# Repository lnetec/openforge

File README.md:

# openforge
OpenForge is Beaglebone Black clone in Kicad.

BeagleBone® Black Industrial answers the need for an industrial rated single board computer with extended temperature range of -40°C to +85°C.
This project aims to bring Beaglebone Black to Kicad ,an excellent open source EDA, world.

Current status:
1. All schematics have been ported to kicad. Component references match original Beaglebone Black.
2. Footprints assigned to all parts.
3. PCB have been created, all componets placed automatically with the help of a python script.

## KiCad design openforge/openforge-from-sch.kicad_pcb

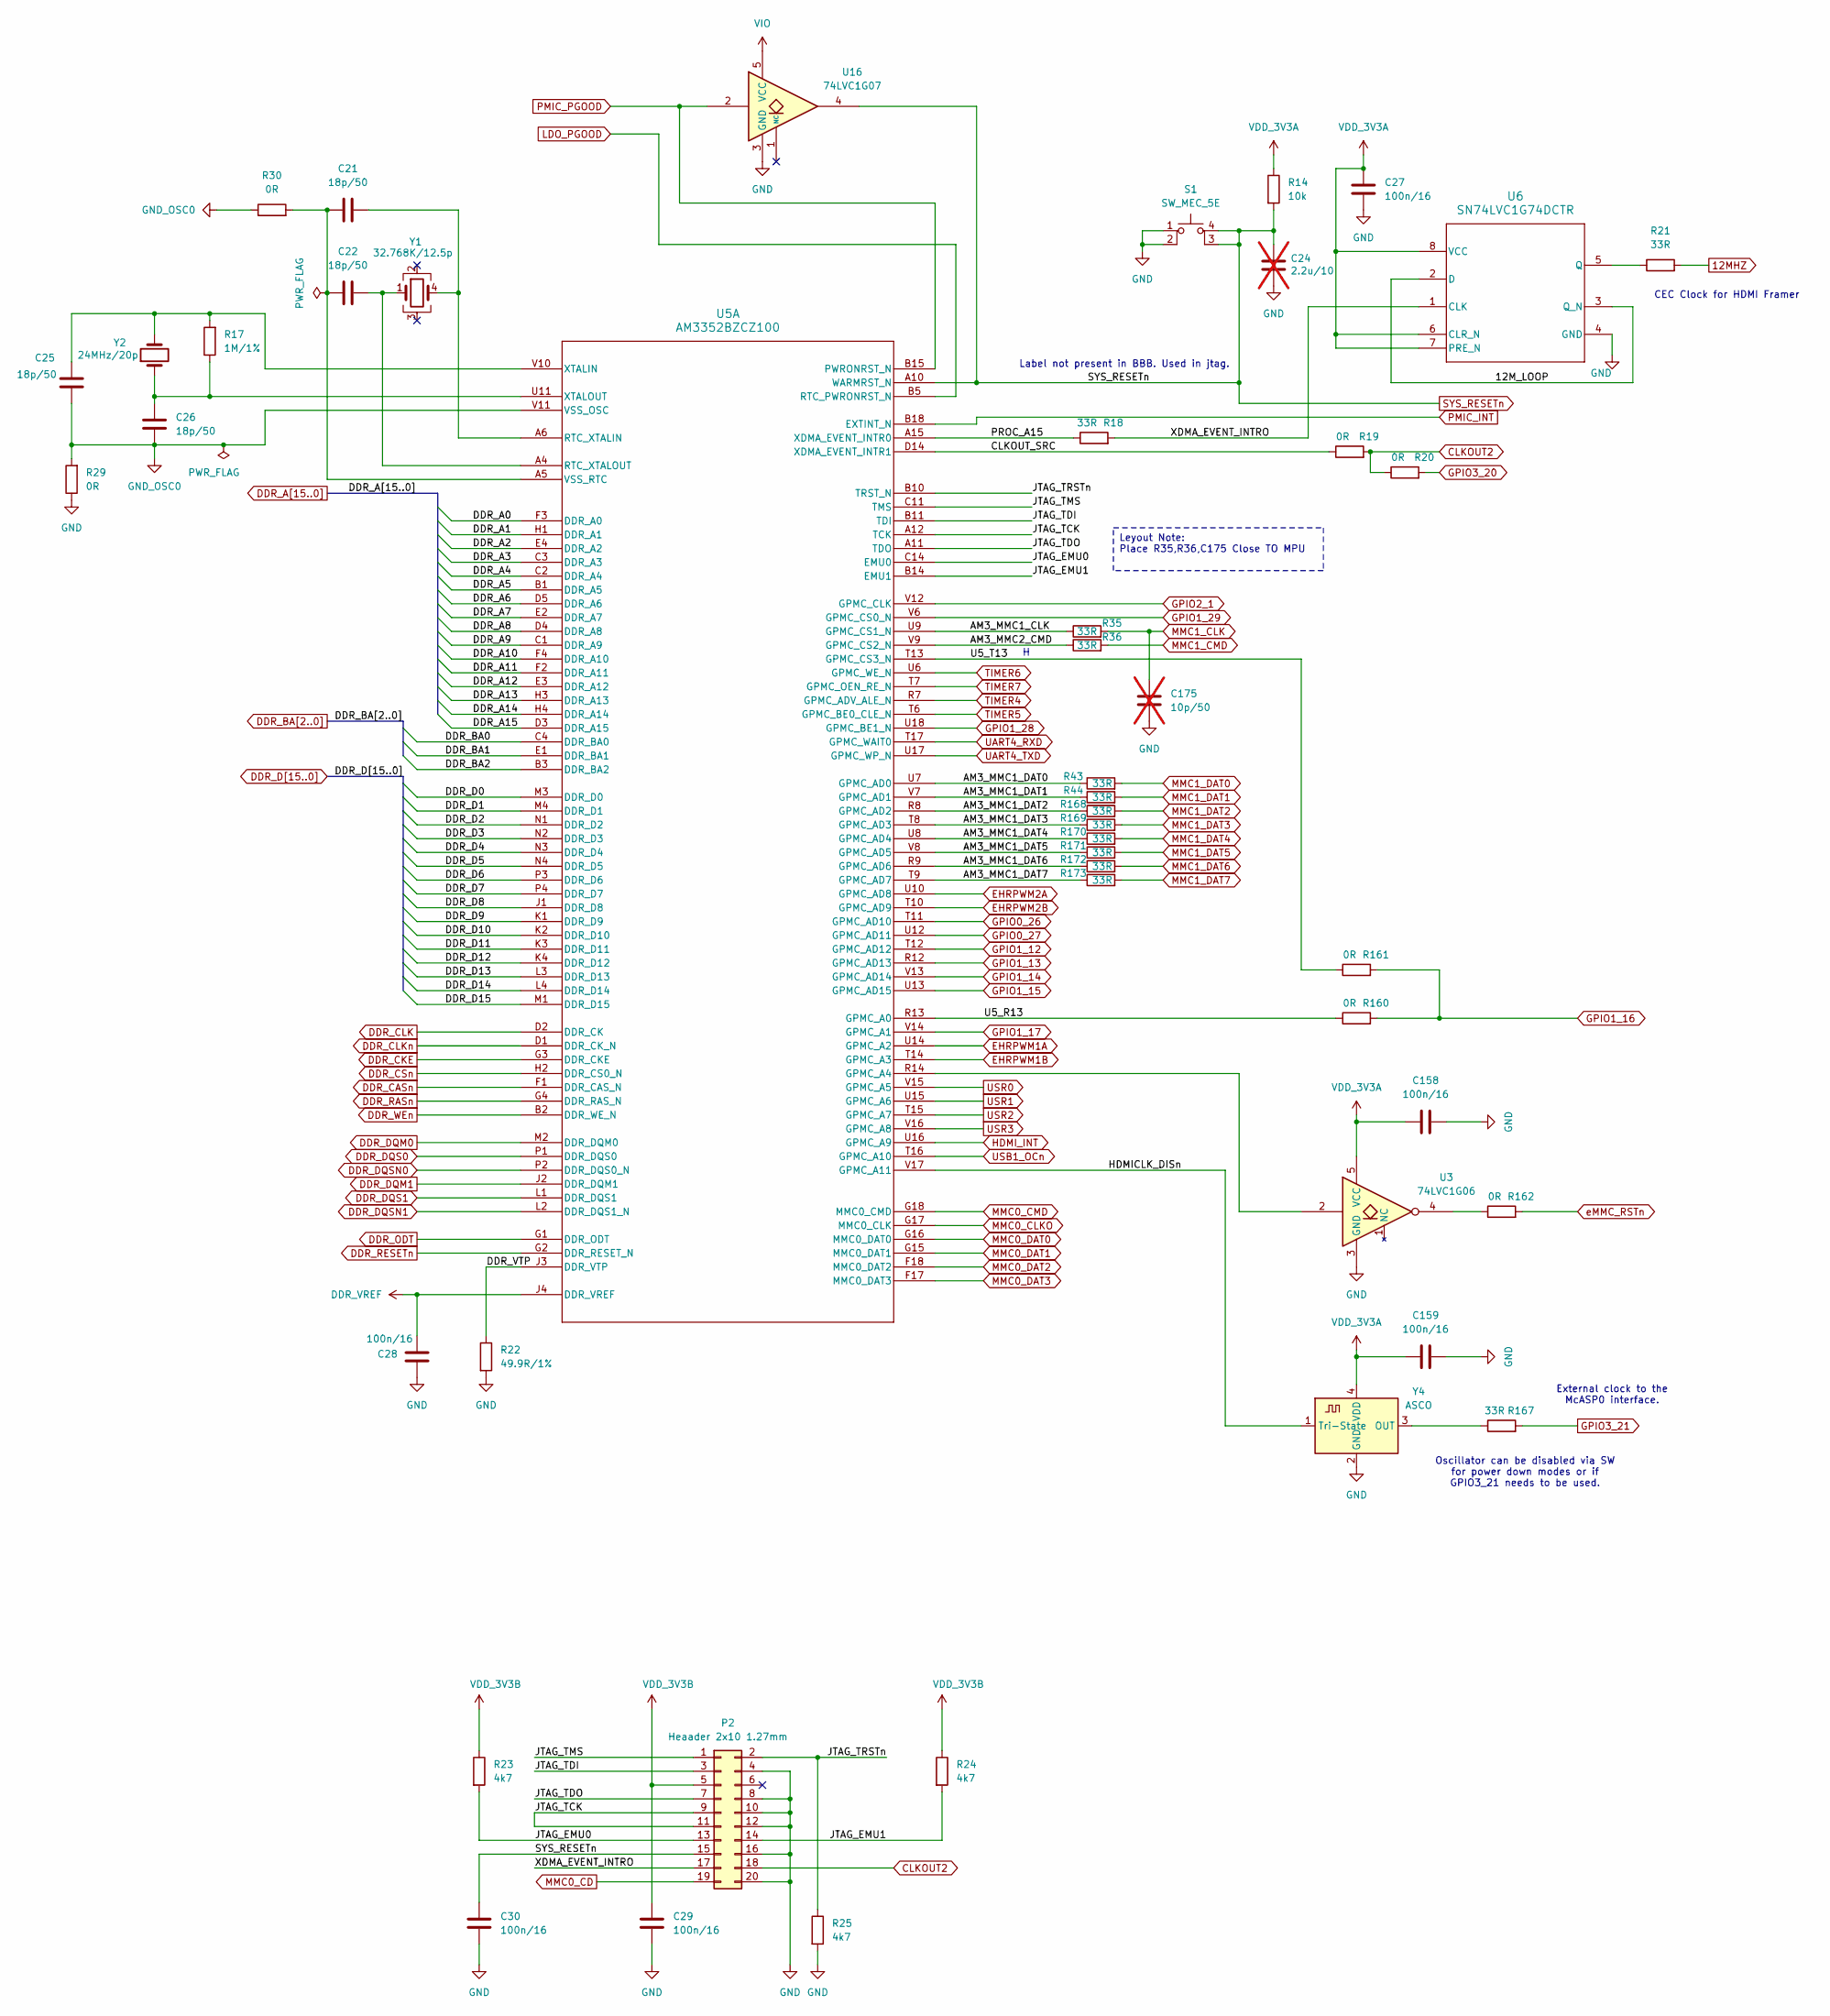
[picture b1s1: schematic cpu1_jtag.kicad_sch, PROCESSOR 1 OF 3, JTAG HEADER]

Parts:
C21, C22, C25, C26: 18p/50; C_0402_1005Metric
C24: 2.2u/10; C_0402_1005Metric; not fitted
C27, C28, C29, C30, C158, C159: 100n/16; C_0402_1005Metric
C175: 10p/50; C_0402_1005Metric; not fitted
P2: Heaader 2x10 1.27mm; PinHeader_2x10_P1.27mm_Vertical_SMD
R14: 10k; R_0402_1005Metric
R17: 1M/1%; R_0402_1005Metric
R18, R21, R35, R36, R43, R44, R167, R168, R169, R170, R171, R172, R173: 33R; R_0402_1005Metric
R19, R20, R29, R30, R160, R161, R162: 0R; R_0402_1005Metric
R22: 49.9R/1%; R_0402_1005Metric
R23, R24, R25: 4k7; R_0402_1005Metric
S1: SW_MEC_5E; KMR2xxG_CNK
U3: 74LVC1G06; DCK0005A_L
U5: AM3352BZCZ100; ZCZ0324A
U6: SN74LVC1G74DCTR; DCT0008A_L
U16: 74LVC1G07; DCK0005A_L
Y1: 32.768K/12.5p; Crystal_SMD_5032-4Pin_5.0x3.2mm
Y2: 24MHz/20p; Crystal_SMD_Abracon_ABM7-2Pin_6.0x3.5mm
Y4: ASCO; Oscillator_SMD_Abracon_ASCO-4Pin_1.6x1.2mm

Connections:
12MHZ: R21.2; also elsewhere on the board
/CPU1 And JTAG/12M_LOOP: U6.2 (D), U6.3 (Q_N)
/CPU1 And JTAG/AM3_MMC1_CLK: R35.1, U5.U9 (GPMC_CS1_N)
/CPU1 And JTAG/AM3_MMC1_DAT0: R43.1, U5.U7 (GPMC_AD0)
/CPU1 And JTAG/AM3_MMC1_DAT1: R44.1, U5.V7 (GPMC_AD1)
/CPU1 And JTAG/AM3_MMC1_DAT2: R168.1, U5.R8 (GPMC_AD2)
/CPU1 And JTAG/AM3_MMC1_DAT3: R169.1, U5.T8 (GPMC_AD3)
/CPU1 And JTAG/AM3_MMC1_DAT4: R170.1, U5.U8 (GPMC_AD4)
/CPU1 And JTAG/AM3_MMC1_DAT5: R171.1, U5.V8 (GPMC_AD5)
/CPU1 And JTAG/AM3_MMC1_DAT6: R172.1, U5.R9 (GPMC_AD6)
/CPU1 And JTAG/AM3_MMC1_DAT7: R173.1, U5.T9 (GPMC_AD7)
/CPU1 And JTAG/AM3_MMC2_CMD: R36.1, U5.V9 (GPMC_CS2_N)
/CPU1 And JTAG/CLKOUT_SRC: R19.1, U5.D14 (XDMA_EVENT_INTR1)
/CPU1 And JTAG/DDR_VTP: R22.1, U5.J3 (DDR_VTP)
/CPU1 And JTAG/HDMICLK_DISn: U5.V17 (GPMC_A11), Y4.1 (Tri-State)
/CPU1 And JTAG/JTAG_EMU0: P2.13, R23.2, U5.C14 (EMU0)
/CPU1 And JTAG/JTAG_EMU1: P2.14, R24.2, U5.B14 (EMU1)
/CPU1 And JTAG/JTAG_TCK: P2.9, P2.11, U5.A12 (TCK)
/CPU1 And JTAG/JTAG_TDI: P2.3, U5.B11 (TDI)
/CPU1 And JTAG/JTAG_TDO: P2.7, U5.A11 (TDO)
/CPU1 And JTAG/JTAG_TMS: P2.1, U5.C11 (TMS)
/CPU1 And JTAG/JTAG_TRSTn: P2.2, R25.1, U5.B10 (TRST_N)
/CPU1 And JTAG/PROC_A15: R18.1, U5.A15 (XDMA_EVENT_INTR0)
/CPU1 And JTAG/U5_R13: R160.1, U5.R13 (GPMC_A0)
/CPU1 And JTAG/U5_T13: R161.1, U5.T13 (GPMC_CS3_N)
/CPU1 And JTAG/XDMA_EVENT_INTRO: P2.17, R18.2, U6.1 (CLK)
CLKOUT2: P2.18, R19.2, R20.1; also elsewhere on the board
DDR_A0: U5.F3 (DDR_A0); also elsewhere on the board
DDR_A1: U5.H1 (DDR_A1); also elsewhere on the board
DDR_A2: U5.E4 (DDR_A2); also elsewhere on the board
DDR_A3: U5.C3 (DDR_A3); also elsewhere on the board
DDR_A4: U5.C2 (DDR_A4); also elsewhere on the board
DDR_A5: U5.B1 (DDR_A5); also elsewhere on the board
DDR_A6: U5.D5 (DDR_A6); also elsewhere on the board
DDR_A7: U5.E2 (DDR_A7); also elsewhere on the board
DDR_A8: U5.D4 (DDR_A8); also elsewhere on the board
DDR_A9: U5.C1 (DDR_A9); also elsewhere on the board
DDR_A10: U5.F4 (DDR_A10); also elsewhere on the board
DDR_A11: U5.F2 (DDR_A11); also elsewhere on the board
DDR_A12: U5.E3 (DDR_A12); also elsewhere on the board
DDR_A13: U5.H3 (DDR_A13); also elsewhere on the board
DDR_A14: U5.H4 (DDR_A14); also elsewhere on the board
DDR_A15: U5.D3 (DDR_A15); also elsewhere on the board
DDR_BA0: U5.C4 (DDR_BA0); also elsewhere on the board
DDR_BA1: U5.E1 (DDR_BA1); also elsewhere on the board
DDR_BA2: U5.B3 (DDR_BA2); also elsewhere on the board
DDR_CASn: U5.F1 (DDR_CAS_N); also elsewhere on the board
DDR_CKE: U5.G3 (DDR_CKE); also elsewhere on the board
DDR_CLK: U5.D2 (DDR_CK); also elsewhere on the board
DDR_CLKn: U5.D1 (DDR_CK_N); also elsewhere on the board
DDR_CSn: U5.H2 (DDR_CS0_N); also elsewhere on the board
DDR_D0: U5.M3 (DDR_D0); also elsewhere on the board
DDR_D1: U5.M4 (DDR_D1); also elsewhere on the board
DDR_D2: U5.N1 (DDR_D2); also elsewhere on the board
DDR_D3: U5.N2 (DDR_D3); also elsewhere on the board
DDR_D4: U5.N3 (DDR_D4); also elsewhere on the board
DDR_D5: U5.N4 (DDR_D5); also elsewhere on the board
DDR_D6: U5.P3 (DDR_D6); also elsewhere on the board
DDR_D7: U5.P4 (DDR_D7); also elsewhere on the board
DDR_D8: U5.J1 (DDR_D8); also elsewhere on the board
DDR_D9: U5.K1 (DDR_D9); also elsewhere on the board
DDR_D10: U5.K2 (DDR_D10); also elsewhere on the board
DDR_D11: U5.K3 (DDR_D11); also elsewhere on the board
DDR_D12: U5.K4 (DDR_D12); also elsewhere on the board
DDR_D13: U5.L3 (DDR_D13); also elsewhere on the board
DDR_D14: U5.L4 (DDR_D14); also elsewhere on the board
DDR_D15: U5.M1 (DDR_D15); also elsewhere on the board
DDR_DQM0: U5.M2 (DDR_DQM0); also elsewhere on the board
DDR_DQM1: U5.J2 (DDR_DQM1); also elsewhere on the board
DDR_DQS0: U5.P1 (DDR_DQS0); also elsewhere on the board
DDR_DQS1: U5.L1 (DDR_DQS1); also elsewhere on the board
DDR_DQSN0: U5.P2 (DDR_DQS0_N); also elsewhere on the board
DDR_DQSN1: U5.L2 (DDR_DQS1_N); also elsewhere on the board
DDR_ODT: U5.G1 (DDR_ODT); also elsewhere on the board
DDR_RASn: U5.G4 (DDR_RAS_N); also elsewhere on the board
DDR_RESETn: U5.G2 (DDR_RESET_N); also elsewhere on the board
DDR_VREF: C28.1, U5.J4 (DDR_VREF); also elsewhere on the board
DDR_WEn: U5.B2 (DDR_WE_N); also elsewhere on the board
EHRPWM1A: U5.U14 (GPMC_A2); also elsewhere on the board
EHRPWM1B: U5.T14 (GPMC_A3); also elsewhere on the board
EHRPWM2A: U5.U10 (GPMC_AD8); also elsewhere on the board
EHRPWM2B: U5.T10 (GPMC_AD9); also elsewhere on the board
GND: C24.2, C27.2, C28.2, C29.1, C30.1, C158.2, C159.2, C175.2, P2.4, P2.8, P2.10, P2.12, P2.16, P2.20, R22.2, R25.2, R29.1, S1.1, S1.2, U3.3 (GND), U6.4 (GND), U16.3 (GND), Y4.2 (GND); also elsewhere on the board
GND_OSC0: C25.1, C26.1, R29.2, R30.1, U5.V11 (VSS_OSC)
GPIO0_26: U5.T11 (GPMC_AD10); also elsewhere on the board
GPIO0_27: U5.U12 (GPMC_AD11); also elsewhere on the board
GPIO1_12: U5.T12 (GPMC_AD12); also elsewhere on the board
GPIO1_13: U5.R12 (GPMC_AD13); also elsewhere on the board
GPIO1_14: U5.V13 (GPMC_AD14); also elsewhere on the board
GPIO1_15: U5.U13 (GPMC_AD15); also elsewhere on the board
GPIO1_16: R160.2, R161.2; also elsewhere on the board
GPIO1_17: U5.V14 (GPMC_A1); also elsewhere on the board
GPIO1_28: U5.U18 (GPMC_BE1_N); also elsewhere on the board
GPIO1_29: U5.V6 (GPMC_CS0_N); also elsewhere on the board
GPIO2_1: U5.V12 (GPMC_CLK); also elsewhere on the board
GPIO3_20: R20.2; also elsewhere on the board
GPIO3_21: R167.2; also elsewhere on the board
HDMI_INT: U5.U16 (GPMC_A9); also elsewhere on the board
LDO_PGOOD: U5.B5 (RTC_PWRONRST_N); also elsewhere on the board
MMC0_CD: P2.19; also elsewhere on the board
MMC0_CLKO: U5.G17 (MMC0_CLK); also elsewhere on the board
MMC0_CMD: U5.G18 (MMC0_CMD); also elsewhere on the board
MMC0_DAT0: U5.G16 (MMC0_DAT0); also elsewhere on the board
MMC0_DAT1: U5.G15 (MMC0_DAT1); also elsewhere on the board
MMC0_DAT2: U5.F18 (MMC0_DAT2); also elsewhere on the board
MMC0_DAT3: U5.F17 (MMC0_DAT3); also elsewhere on the board
MMC1_CLK: C175.1, R35.2; also elsewhere on the board
MMC1_CMD: R36.2; also elsewhere on the board
MMC1_DAT0: R43.2; also elsewhere on the board
MMC1_DAT1: R44.2; also elsewhere on the board
MMC1_DAT2: R168.2; also elsewhere on the board
MMC1_DAT3: R169.2; also elsewhere on the board
MMC1_DAT4: R170.2; also elsewhere on the board
MMC1_DAT5: R171.2; also elsewhere on the board
MMC1_DAT6: R172.2; also elsewhere on the board
MMC1_DAT7: R173.2; also elsewhere on the board
unnamed: R162.1, U3.4
unnamed: U3.2, U5.R14 (GPMC_A4)
unnamed: C21.2, U5.A6 (RTC_XTALIN), Y1.4
unnamed: C22.2, U5.A4 (RTC_XTALOUT), Y1.1
unnamed: C21.1, C22.1, R30.2, U5.A5 (VSS_RTC)
unnamed: C25.2, R17.2, U5.V10 (XTALIN), Y2.2
unnamed: C26.2, R17.1, U5.U11 (XTALOUT), Y2.1
unnamed: R21.1, U6.5 (Q)
unnamed: R167.1, Y4.3 (OUT)
PMIC_INT: U5.B18 (EXTINT_N); also elsewhere on the board
PMIC_PGOOD: U5.B15 (PWRONRST_N), U16.2; also elsewhere on the board
SYS_RESETn: C24.1, C30.2, P2.15, R14.2, S1.3 (K), S1.4 (A), U5.A10 (WARMRST_N), U16.4; also elsewhere on the board
TIMER4: U5.R7 (GPMC_ADV_ALE_N); also elsewhere on the board
TIMER5: U5.T6 (GPMC_BE0_CLE_N); also elsewhere on the board
TIMER6: U5.U6 (GPMC_WE_N); also elsewhere on the board
TIMER7: U5.T7 (GPMC_OEN_RE_N); also elsewhere on the board
UART4_RXD: U5.T17 (GPMC_WAIT0); also elsewhere on the board
UART4_TXD: U5.U17 (GPMC_WP_N); also elsewhere on the board
USB1_OCn: U5.T16 (GPMC_A10); also elsewhere on the board
USR0: U5.V15 (GPMC_A5); also elsewhere on the board
USR1: U5.U15 (GPMC_A6); also elsewhere on the board
USR2: U5.T15 (GPMC_A7); also elsewhere on the board
USR3: U5.V16 (GPMC_A8); also elsewhere on the board
VDD_3V3A: C27.1, C158.1, C159.1, R14.1, U3.5 (VCC), U6.6 (CLR_N), U6.7 (PRE_N), U6.8 (VCC), Y4.4 (VDD); also elsewhere on the board
VDD_3V3B: C29.2, P2.5, R23.1, R24.1; also elsewhere on the board
VIO: U16.5 (VCC); also elsewhere on the board
eMMC_RSTn: R162.2; also elsewhere on the board

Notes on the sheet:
Leyout Note: Place R35,R36,C175 Close TO MPU
External clock to the McASP0 interface.
CEC Clock for HDMI Framer
Label not present in BBB. Used in jtag.
Oscillator can be disabled via SW for power down modes or if GPIO3_21 needs to be used.

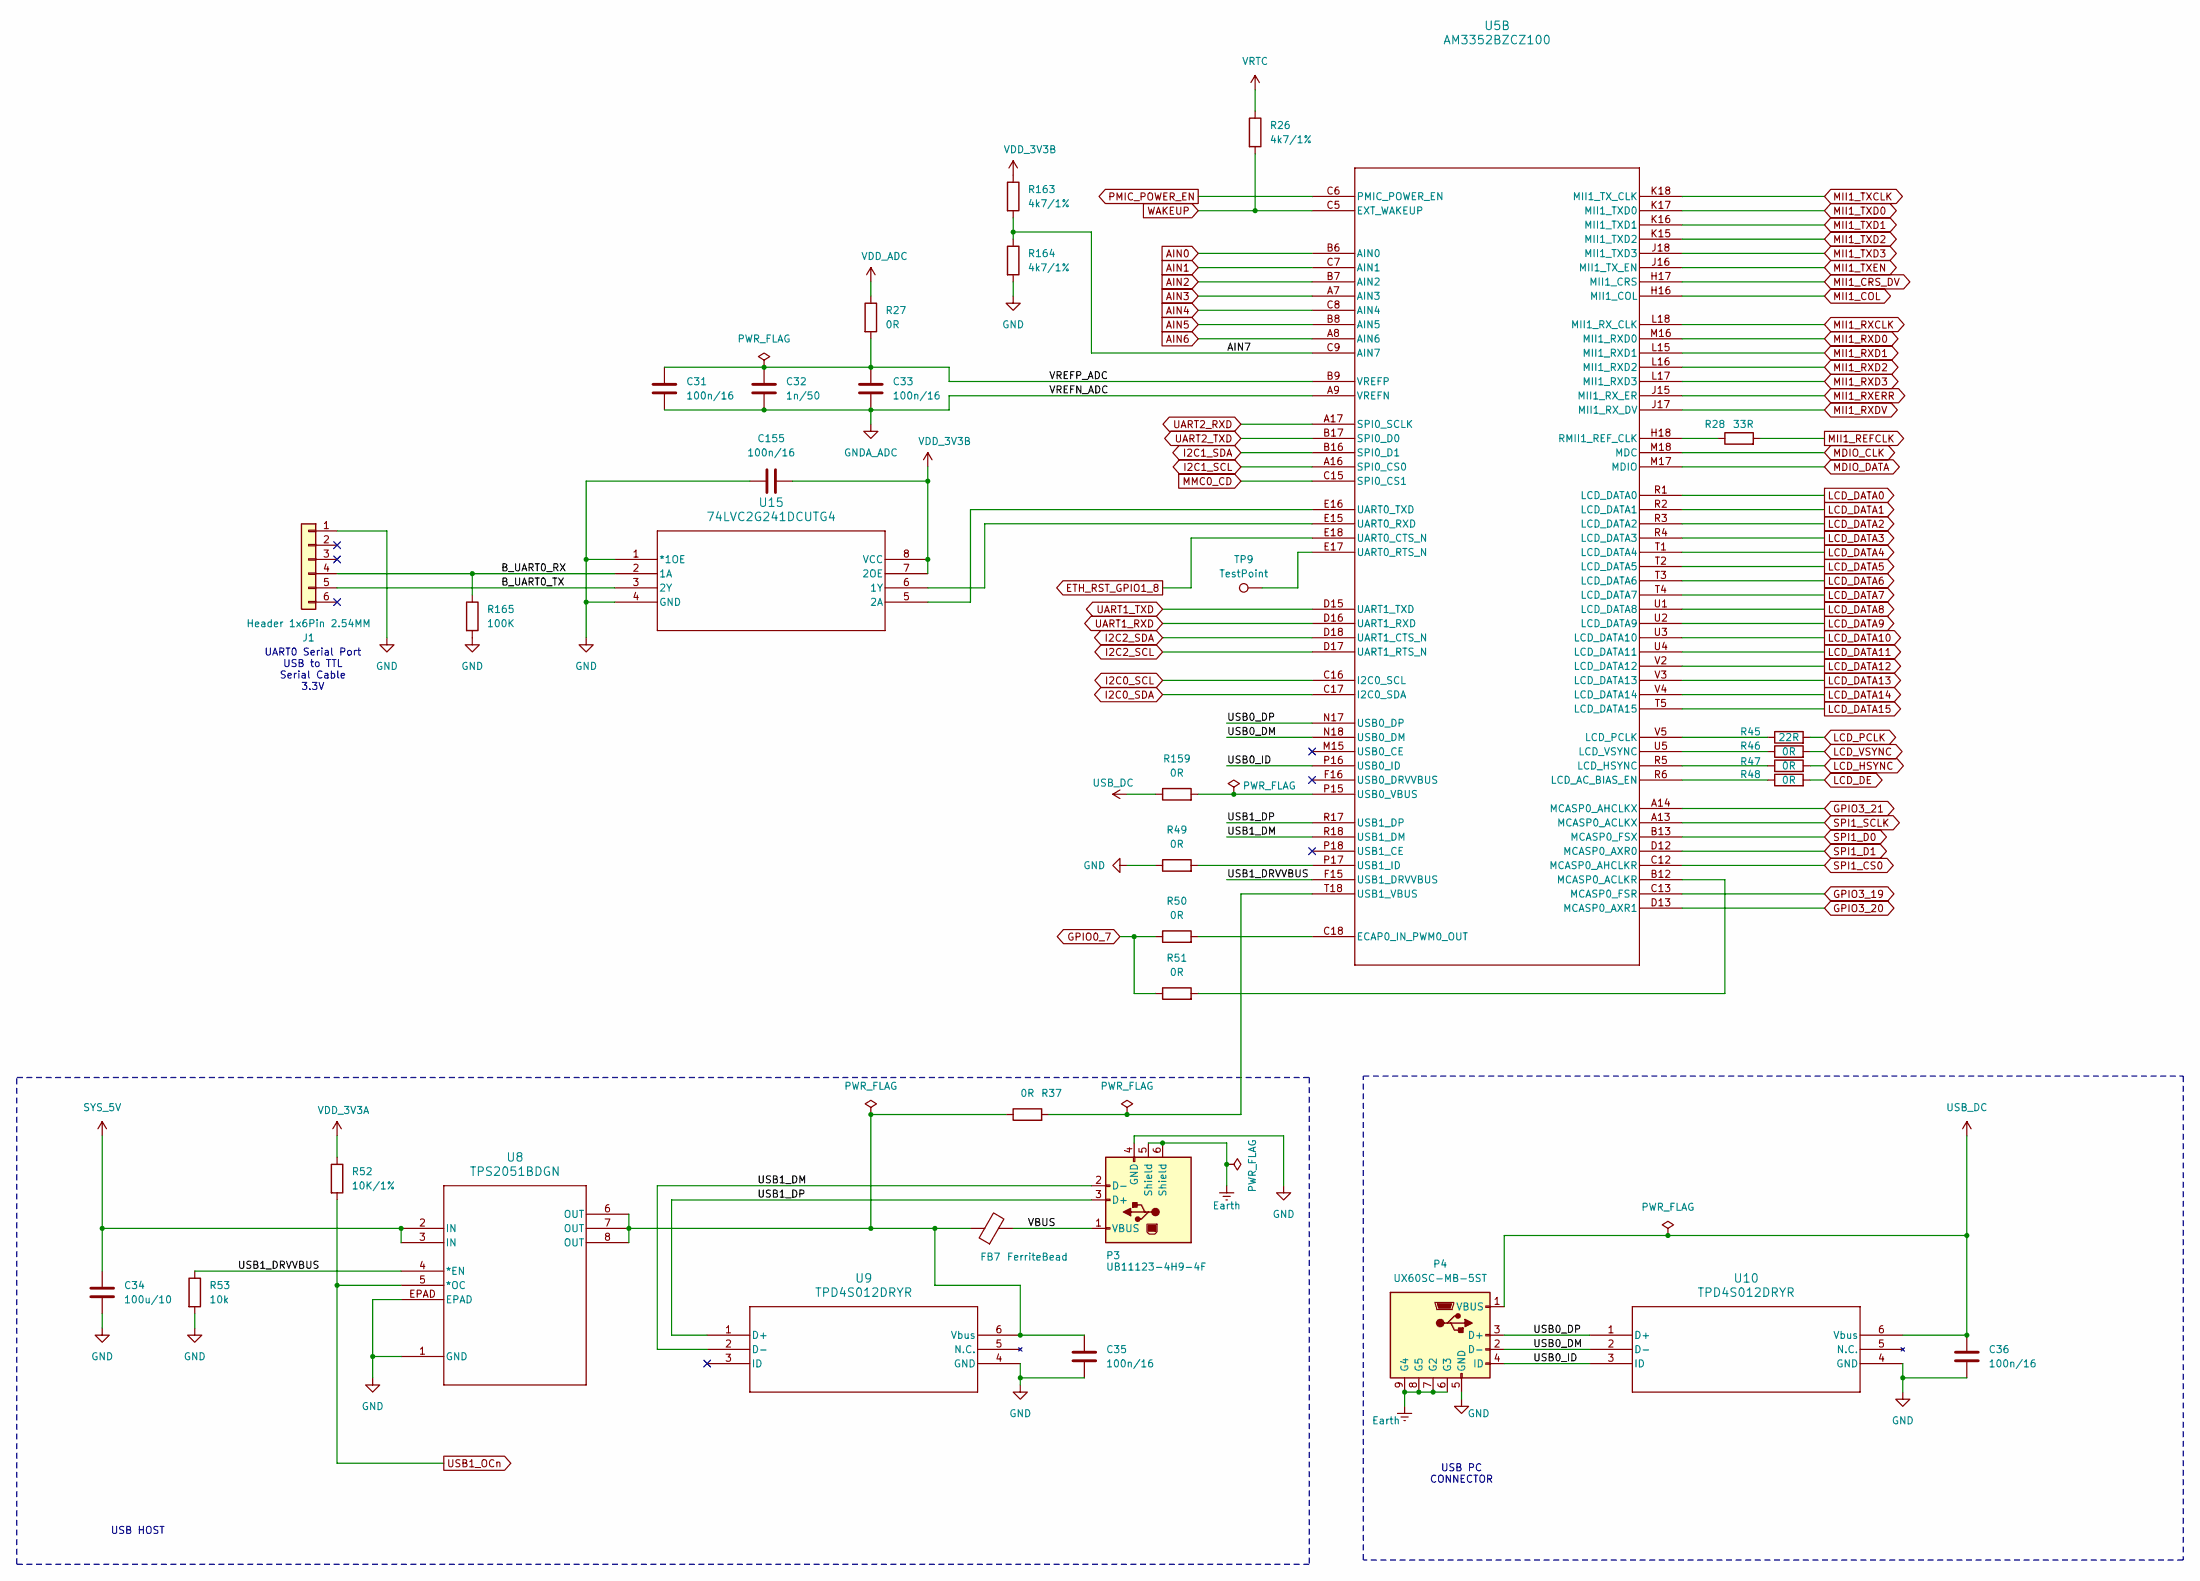
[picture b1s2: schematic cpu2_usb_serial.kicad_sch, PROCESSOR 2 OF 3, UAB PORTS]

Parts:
C31, C33, C35, C36, C155: 100n/16; C_0402_1005Metric
C32: 1n/50; C_0402_1005Metric
C34: 100u/10; C_0805_2012Metric
FB7: FerriteBead; L_0805_2012Metric
J1: Header 1x6Pin 2.54MM; PinHeader_1x06_P2.54mm_Vertical
P3: UB11123-4H9-4F; CONN4_87520-0010_FCI
P4: UX60SC-MB-5ST; CONN_MB-5ST80
R26, R163, R164: 4k7/1%; R_0402_1005Metric
R27, R37, R46, R47, R48, R49, R50, R51, R159: 0R; R_0402_1005Metric
R28: 33R; R_0402_1005Metric
R45: 22R; R_0402_1005Metric
R52: 10K/1%; R_0402_1005Metric
R53: 10k; R_0402_1005Metric
R165: 100K; R_0402_1005Metric
TP9: TestPoint; TestPoint_Pad_1.5x1.5mm
U5: AM3352BZCZ100; ZCZ0324A
U8: TPS2051BDGN; DGN8_1P89X1P57
U9, U10: TPD4S012DRYR; DRY6
U15: 74LVC2G241DCUTG4; DCT8

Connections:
/CPU2, USB AND Serial/AIN7: R163.2, R164.1, U5.C9 (AIN7)
/CPU2, USB AND Serial/B_UART0_RX: J1.4, R165.1, U15.2 (1A)
/CPU2, USB AND Serial/B_UART0_TX: J1.5, U15.3 (2Y)
/CPU2, USB AND Serial/USB0_DM: P4.2 (D-), U5.N18 (USB0_DM), U10.2 (D-)
/CPU2, USB AND Serial/USB0_DP: P4.3 (D+), U5.N17 (USB0_DP), U10.1 (D+)
/CPU2, USB AND Serial/USB0_ID: P4.4 (ID), U5.P16 (USB0_ID), U10.3 (ID)
/CPU2, USB AND Serial/USB1_DM: P3.2 (D-), U5.R18 (USB1_DM), U9.2 (D-)
/CPU2, USB AND Serial/USB1_DP: P3.3 (D+), U5.R17 (USB1_DP), U9.1 (D+)
/CPU2, USB AND Serial/USB1_DRVVBUS: R53.1, U5.F15 (USB1_DRVVBUS), U8.4 (*EN)
/CPU2, USB AND Serial/VBUS: FB7.2, P3.1 (VBUS)
/CPU2, USB AND Serial/VREFP_ADC: C31.1, C32.1, C33.1, R27.2, U5.B9 (VREFP)
AIN0: U5.B6 (AIN0); also elsewhere on the board
AIN1: U5.C7 (AIN1); also elsewhere on the board
AIN2: U5.B7 (AIN2); also elsewhere on the board
AIN3: U5.A7 (AIN3); also elsewhere on the board
AIN4: U5.C8 (AIN4); also elsewhere on the board
AIN5: U5.B8 (AIN5); also elsewhere on the board
AIN6: U5.A8 (AIN6); also elsewhere on the board
ETH_RST_GPIO1_8: U5.E18 (UART0_CTS_N); also elsewhere on the board
Earth: P3.5 (Shield), P3.6 (Shield), P4.6 (G3), P4.7 (G2), P4.8 (G5), P4.9 (G4); also elsewhere on the board
GND: C34.2, C35.2, C36.2, C155.1, J1.1, P3.4 (GND), P4.5 (GND), R49.1, R53.2, R164.2, R165.2, U8.1 (GND), U8.EPAD, U9.4 (GND), U10.4 (GND), U15.1 (*1OE), U15.4 (GND); also elsewhere on the board
GNDA_ADC: C31.2, C32.2, C33.2, U5.A9 (VREFN); also elsewhere on the board
GPIO0_7: R50.1, R51.1; also elsewhere on the board
GPIO3_19: U5.C13 (MCASP0_FSR); also elsewhere on the board
GPIO3_20: U5.D13 (MCASP0_AXR1); also elsewhere on the board
GPIO3_21: U5.A14 (MCASP0_AHCLKX); also elsewhere on the board
I2C0_SCL: U5.C16 (I2C0_SCL); also elsewhere on the board
I2C0_SDA: U5.C17 (I2C0_SDA); also elsewhere on the board
I2C1_SCL: U5.A16 (SPI0_CS0); also elsewhere on the board
I2C1_SDA: U5.B16 (SPI0_D1); also elsewhere on the board
I2C2_SCL: U5.D17 (UART1_RTS_N); also elsewhere on the board
I2C2_SDA: U5.D18 (UART1_CTS_N); also elsewhere on the board
LCD_DATA0: U5.R1 (LCD_DATA0); also elsewhere on the board
LCD_DATA1: U5.R2 (LCD_DATA1); also elsewhere on the board
LCD_DATA2: U5.R3 (LCD_DATA2); also elsewhere on the board
LCD_DATA3: U5.R4 (LCD_DATA3); also elsewhere on the board
LCD_DATA4: U5.T1 (LCD_DATA4); also elsewhere on the board
LCD_DATA5: U5.T2 (LCD_DATA5); also elsewhere on the board
LCD_DATA6: U5.T3 (LCD_DATA6); also elsewhere on the board
LCD_DATA7: U5.T4 (LCD_DATA7); also elsewhere on the board
LCD_DATA8: U5.U1 (LCD_DATA8); also elsewhere on the board
LCD_DATA9: U5.U2 (LCD_DATA9); also elsewhere on the board
LCD_DATA10: U5.U3 (LCD_DATA10); also elsewhere on the board
LCD_DATA11: U5.U4 (LCD_DATA11); also elsewhere on the board
LCD_DATA12: U5.V2 (LCD_DATA12); also elsewhere on the board
LCD_DATA13: U5.V3 (LCD_DATA13); also elsewhere on the board
LCD_DATA14: U5.V4 (LCD_DATA14); also elsewhere on the board
LCD_DATA15: U5.T5 (LCD_DATA15); also elsewhere on the board
LCD_DE: R48.2; also elsewhere on the board
LCD_HSYNC: R47.2; also elsewhere on the board
LCD_PCLK: R45.2; also elsewhere on the board
LCD_VSYNC: R46.2; also elsewhere on the board
MDIO_CLK: U5.M18 (MDC); also elsewhere on the board
MDIO_DATA: U5.M17 (MDIO); also elsewhere on the board
MII1_COL: U5.H16 (MII1_COL); also elsewhere on the board
MII1_CRS_DV: U5.H17 (MII1_CRS); also elsewhere on the board
MII1_REFCLK: R28.2; also elsewhere on the board
MII1_RXCLK: U5.L18 (MII1_RX_CLK); also elsewhere on the board
MII1_RXD0: U5.M16 (MII1_RXD0); also elsewhere on the board
MII1_RXD1: U5.L15 (MII1_RXD1); also elsewhere on the board
MII1_RXD2: U5.L16 (MII1_RXD2); also elsewhere on the board
MII1_RXD3: U5.L17 (MII1_RXD3); also elsewhere on the board
MII1_RXDV: U5.J17 (MII1_RX_DV); also elsewhere on the board
MII1_RXERR: U5.J15 (MII1_RX_ER); also elsewhere on the board
MII1_TXCLK: U5.K18 (MII1_TX_CLK); also elsewhere on the board
MII1_TXD0: U5.K17 (MII1_TXD0); also elsewhere on the board
MII1_TXD1: U5.K16 (MII1_TXD1); also elsewhere on the board
MII1_TXD2: U5.K15 (MII1_TXD2); also elsewhere on the board
MII1_TXD3: U5.J18 (MII1_TXD3); also elsewhere on the board
MII1_TXEN: U5.J16 (MII1_TX_EN); also elsewhere on the board
MMC0_CD: U5.C15 (SPI0_CS1); also elsewhere on the board
unnamed: R50.2, U5.C18 (ECAP0_IN_PWM0_OUT)
unnamed: R48.1, U5.R6 (LCD_AC_BIAS_EN)
unnamed: R47.1, U5.R5 (LCD_HSYNC)
unnamed: R45.1, U5.V5 (LCD_PCLK)
unnamed: R46.1, U5.U5 (LCD_VSYNC)
unnamed: R51.2, U5.B12 (MCASP0_ACLKR)
unnamed: R28.1, U5.H18 (RMII1_REF_CLK)
unnamed: TP9.1, U5.E17 (UART0_RTS_N)
unnamed: R159.2, U5.P15 (USB0_VBUS)
unnamed: R49.2, U5.P17 (USB1_ID)
unnamed: R37.2, U5.T18 (USB1_VBUS)
unnamed: C35.1, FB7.1, R37.1, U8.6 (OUT), U8.7 (OUT), U8.8 (OUT), U9.6 (Vbus)
unnamed: U5.E15 (UART0_RXD), U15.6 (1Y)
unnamed: U5.E16 (UART0_TXD), U15.5 (2A)
PMIC_POWER_EN: U5.C6 (PMIC_POWER_EN); also elsewhere on the board
SPI1_CS0: U5.C12 (MCASP0_AHCLKR); also elsewhere on the board
SPI1_D0: U5.B13 (MCASP0_FSX); also elsewhere on the board
SPI1_D1: U5.D12 (MCASP0_AXR0); also elsewhere on the board
SPI1_SCLK: U5.A13 (MCASP0_ACLKX); also elsewhere on the board
SYS_5V: C34.1, U8.2 (IN), U8.3 (IN); also elsewhere on the board
UART1_RXD: U5.D16 (UART1_RXD); also elsewhere on the board
UART1_TXD: U5.D15 (UART1_TXD); also elsewhere on the board
UART2_RXD: U5.A17 (SPI0_SCLK); also elsewhere on the board
UART2_TXD: U5.B17 (SPI0_D0); also elsewhere on the board
USB1_OCn: R52.2, U8.5 (*OC); also elsewhere on the board
USB_DC: C36.1, P4.1 (VBUS), R159.1, U10.6 (Vbus); also elsewhere on the board
VDD_3V3A: R52.1; also elsewhere on the board
VDD_3V3B: C155.2, R163.1, U15.7 (2OE), U15.8 (VCC); also elsewhere on the board
VDD_ADC: R27.1; also elsewhere on the board
VRTC: R26.1; also elsewhere on the board
WAKEUP: R26.2, U5.C5 (EXT_WAKEUP); also elsewhere on the board

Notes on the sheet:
USB HOST
USB PC CONNECTOR
UART0 Serial Port USB to TTL Serial Cable 3.3V
